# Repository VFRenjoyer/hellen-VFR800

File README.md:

This repo contains files to build a standalone plug and play RusEFI Hellen based ECU for a 99 Honda VFR800. The prototype is unfinished and currently none of these files can be used to make a functioning ECU

This hardware may be compatible with the CBR600F4i, CBR929RR, and 01-03 CBR1100xx  if the ECU connectors were repinned.

In addition to the above it may be able to replace the ignition module/ECU of a 98-08 VT1100C, 01-07 VT750DC, 02-04 VTX1800, RC51, and 2003-09 VTX1300 with some harness repinning

Features in progress as of v0.05A:

Drop in ECU replacement for 99-01 VFR800 with addition of 2 wideband oxygen sensors

4x sequential ignition/injection

CANBUS

2x Wideband oxygen sensor channels

3x lowside driver output on rear connector

Inputs for analog sensor on rear connector

USB support

Bluetooth connectivity

MicroSD card for logging

VSS input to ECU for eventual implementation of traction control

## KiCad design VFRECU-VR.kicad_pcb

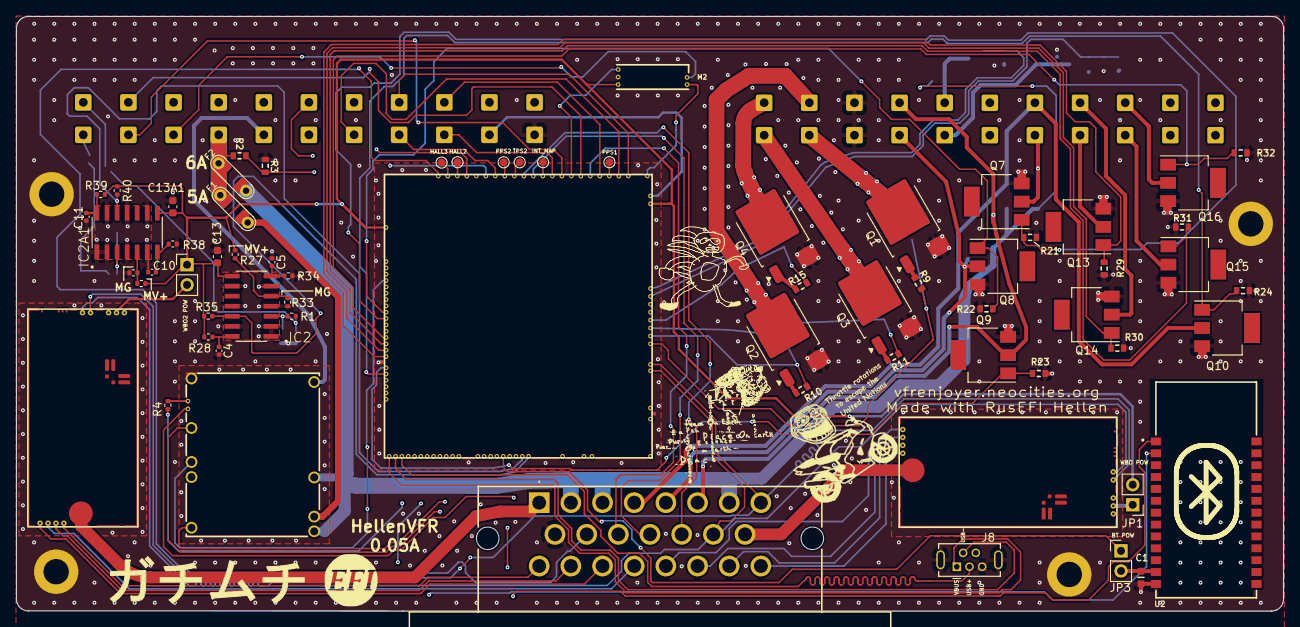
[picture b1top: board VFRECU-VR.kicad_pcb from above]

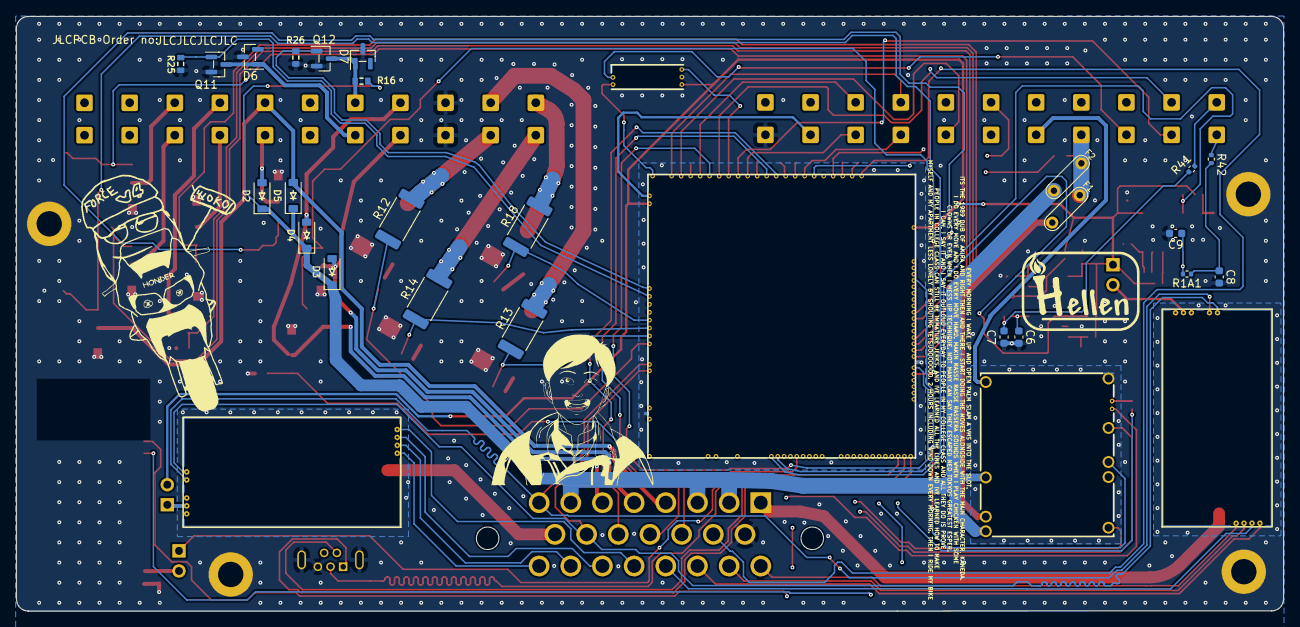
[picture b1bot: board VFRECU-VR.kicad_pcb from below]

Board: 4 copper layers, 160.0 x 75.1 mm, 96 parts (23 on the bottom side), 103 nets.

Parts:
C1: 100n; C0603
C4, C11: 1.2n; C_0402_1005Metric
C5, C10: 0.33u; C_0402_1005Metric
C6, C9: C_0603_1608Metric
C7, C8: 0.33u; C_0603_1608Metric
C13, C13A1: 10u; C_0603_1608Metric
D2, D3, D4, D5: B5819W; SOD-123
D6, D7: PSM712-LF; SOT-23
F1, F2: 12H1500D; PAD-1206-PAD
G3: RUSEFI_LOGO; rusefi_logo
G4: LOGO
H1, H2, H3, H4: MountingHole_Pad; MountingHole_3.2mm_M3_DIN965_Pad
HALL2, HALL3: TestPoint_Pad_D1.0mm
IC2, IC2A1: LM1815MX_NOPB; SOIC127P600X175-14N
INT_MAP: TestPoint_Pad_D1.0mm
J4: 1-776087-1; 17760871
J8: USB_B_Mini; USB-MINI-B-VERTICAL
JP1, JP2, JP3: Jumper_2_Bridged; PinHeader_1x02_P2.54mm_Vertical
M1: Module-power_12and5V-0.2; power_12and5V
M2: Module-knock-0.2; knock
M5, M7: Module-wbo-0.5; wbo
M6: Module:mega-mcu100/0.2; mega-mcu100
PPS1, PPS2: TestPoint_Pad_D1.0mm
Q1, Q2, Q3, Q4: ISL9V3040D3S; TO-252-2
Q7, Q8, Q9, Q10, Q13, Q14, Q15, Q16: ZXMS6005SGTA; SOT-223
Q11, Q12: AO3400A; SOT-23
R1, R1A1: 4.7k; R_0402_1005Metric
R2: 33k; R0603
R3: 6.8k; R0603
R4, R27, R33, R36, R37, R41, R42: 0; R_0402_1005Metric
R9, R10, R11, R15: 22; R0603
R12, R13, R14, R18: 0; R_2512_6332Metric
R16: 470k; R0603
R21, R22, R23, R24, R25, R26, R29, R30, R31, R32: 4.7k; R0603
R28, R39: 100k; R_0402_1005Metric
R34, R38: 1.6M; R_0402_1005Metric
R35, R40: 5.6k; R_0402_1005Metric
TPS2: TestPoint_Pad_D1.0mm
U1: VFRboardempty
U2: JDY-33
text1: trollfaceVFR

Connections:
+3.3VA: JP3.1 (A), M6.N15 (V33_SWITCHABLE)
+5V: M1.E4 (V5), M6.N22 (VCC)
+5VA: C13.2, C13A1.2, IC2.8 (VCC), IC2A1.8 (VCC), JP1.2 (B), JP2.1 (A), M2.E1 (V5A), M6.E1 (V5A_SWITCHABLE), M6.W2 (V5A_SWITCHABLE), R27.1, R28.1, R35.1, R37.1, R39.1, R40.1
+5VP: M1.V4 (5VP), U1.B7
+12V: F1.1, F2.1, R2.2, U1.B8
+12V_RAW: D2.1 (K), D3.1 (K), D4.1 (K), D5.1 (K), F2.2, J4.2, J4.3, J4.7, M1.V1 (V12_PERM), M1.V3 (V12_RAW)
/ADC3: M2.E3 (OUT_KNOCK), M6.S15 (IN_KNOCK_(PA2))
/BARO: M6.S7 (IN_AUX3_(PC5)), U1.B4
/CAM+: R42.1, U1.B11
/CAN+: J4.8, M5.W4 (CANH), M6.W11 (CANH), M7.W4 (CANH)
/CAN-: J4.14, M5.W3 (CANL), M6.W12 (CANL), M7.W3 (CANL)
/CLT: M6.S21 (IN_CLT_(PC2)), U1.B15
/CRANK+: R41.1, U1.B22
/Clutch/kickstandswitch: M6.S16 (IN_CAM_(PA6)), U1.B21
/FILIGHT: D6.1, Q11.2 (D), U1.A7
/FUELPUMP_LS: D2.2 (A), Q7.2 (D), U1.A5
/IAT_SENSOR: M6.S20 (IN_IAT_(PC3)), U1.B5
/IGN1: M6.W10 (IGN1_(PC13)), R9.2, R12.1
/IGN2: M6.W9 (IGN2_(PE5)), R10.2, R13.1
/IGN3: M6.W8 (IGN3_(PE4)), R11.2, R14.1
/IGN4: M6.W7 (IGN4_(PE3)), R15.2, R18.1
/IGNOUT1: Q1.2 (C), R12.2, U1.A10
/IGNOUT2: Q2.2 (C), R13.2, U1.A21
/IGNOUT3: Q3.2 (C), R14.2, U1.A11
/IGNOUT4: Q4.2 (C), R18.2, U1.A22
/INJ1: M6.E17 (OUT_INJ1_(PD3)), Q13.1 (G), R29.2
/INJ2: M6.E16 (OUT_INJ2_(PA9)), Q14.1 (G), R30.2
/INJ3: M6.E15 (OUT_INJ3_(PD11)), Q15.1 (G), R31.2
/INJ4: M6.E14 (OUT_INJ4_(PD10)), Q16.1 (G), R32.2
/INJOUT1: Q13.2 (D), U1.A4
/INJOUT2: Q14.2 (D), U1.A15
/INJOUT3: Q15.2 (D), U1.A3
/INJOUT4: Q16.2 (D), U1.A14
/INTAKEFLAP: D5.2 (A), J4.4, Q10.2 (D), U1.A16
/INTERNAL_MAP: INT_MAP.1, M6.S12 (IN_MAP2_(PC1))
/IN_AUX1: J4.12, M6.S11 (IN_O2S_/_CAN_WAKEUP_(PA0))
/IN_AUX2: J4.13, M6.S10 (IN_O2S2_(PA1))
/IN_BUTTON1: M6.S14 (IN_CRANK_(PB1)), U1.B10
/IN_BUTTON3: J4.10, M6.S1 (IN_D4_(PE15))
/IN_FLEX: J4.11, M6.S17 (IN_VSS_(PE11))
/IN_HALL1: M6.S4 (IN_D1_(PE12)), U1.B17
/IN_HALL2: HALL2.1, M6.S3 (IN_D2_(PE13))
/IN_HALL3: HALL3.1, M6.S2 (IN_D3_(PE14))
/IN_KNOCK_RAW: M2.W1 (IN_KNOCK), U1.B9
/IN_MAP: M6.S13 (IN_MAP1_(PC0)), U1.B3
/IN_PPS1: M6.S19 (IN_PPS_(PA3)), PPS1.1
/IN_PPS2: M6.S8 (IN_AUX2_(PC4/PE9)), PPS2.1
/IN_TPS1: M6.S18 (IN_TPS_(PA4)), U1.B14
/IN_VIGN: F1.2, M1.V2 (IN_VIGN)
/IN_VMAIN: M6.S6 (IN_AUX4_(PA7)), R2.1, R3.2
/LM1815-Cam/Signal+: C8.1, R1A1.1, R42.2
/LM1815-Crank/Signal+: C7.1, R1.1, R41.2
/LS1: M6.E11 (OUT_INJ7_(PD15)), Q7.1 (G), R21.2
/LS2: M6.E10 (OUT_INJ8_(PD12)), Q8.1 (G), R22.2
/LS3: M6.E18 (OUT_PWM1_(PD13)), Q9.1 (G), R23.2
/LS4: M6.E19 (OUT_PWM2_(PC6)), Q10.1 (G), R24.2
/LS_WEAK1: M6.W4 (IGN7_(PB9)), Q11.1 (G), R25.1
/LS_WEAK2: M6.W3 (IGN8_(PE6)), Q12.1 (G), R26.1
/OUT_LS2: D3.2 (A), J4.5, Q8.2 (D), U1.A8
/OUT_LS3: D4.2 (A), J4.6, Q9.2 (D), U1.A19
/OUT_LS_WEAK2: D7.1, Q12.2 (D), R16.1, U1.A18
/PG_5VP: M6.N12 (SPI3_MOSI_(PC12)), R4.2
/PWR_EN: M1.E5 (EN_5VP), M6.N20 (OUT_PWR_EN_(PE10))
/USB+: J8.3 (D+), M6.N3 (USBP_(PA12))
/USB-: J8.2 (D-), M6.N2 (USBM_(PA11))
/VBAT: M1.E1 (VBAT), M6.N17 (VBAT)
/VBUS: J8.1 (VBUS), M6.N1 (VBUS)
/VIGN: M1.E3 (VIGN), M6.E5 (IN_VIGN_(PA5))
/VR1: IC2A1.12 (REFERENCE_PULSE_OUT), M6.N18 (UART8_RX_(PE0)), R40.2
/VR2: IC2.12 (REFERENCE_PULSE_OUT), M6.N19 (UART8_TX_(PE1)), R35.2
/VREF1: M2.W2 (VREF), M6.S22 (VREF1)
/WBO2_Heater: J4.1, M7.E5 (LSU_H+)
/WBO2_Ip: J4.17, M7.E3 (LSU_Ip)
/WBO2_Rtrim: J4.19, M7.E4 (LSU_Rtrim)
/WBO2_Un: J4.18, M7.E1 (LSU_Un)
/WBO2_Vm: J4.16, M7.E2 (LSU_Vm)
/WBO_Heater: J4.15, M5.E5 (LSU_H+)
/WBO_Ip: J4.22, M5.E3 (LSU_Ip)
/WBO_Rtrim: J4.21, M5.E4 (LSU_Rtrim)
/WBO_Un: J4.20, M5.E1 (LSU_Un)
/WBO_Vm: J4.23, M5.E2 (LSU_Vm)
GND: C1.1, C4.2, C5.1, C6.2, C7.2, C8.2, C9.2, C10.1, C11.2, C13.1, C13A1.1, D6.2, D7.2, H1.1, H2.1, H3.1, H4.1, IC2.1 (NC_1), IC2.2 (GND), IC2.4 (NC_2), IC2.6 (NC_3), IC2.9 (TIMING_PULSE_INPUT), IC2.11 (INPUT_SELECT), IC2.13 (NC_4), IC2A1.1 (NC_1), IC2A1.2 (GND), IC2A1.4 (NC_2), IC2A1.6 (NC_3), IC2A1.9 (TIMING_PULSE_INPUT), IC2A1.11 (INPUT_SELECT), IC2A1.13 (NC_4), J4.9, J8.5 (GND), J8.6 (Shield), M1.S1 (GND), M2.E2 (GND), M5.E6 (LSU_H-), M5.G (GND), M6.G (GND), M7.E6 (LSU_H-), M7.G (GND), Q1.3 (E), Q2.3 (E), Q3.3 (E), Q4.3 (E), Q7.3 (S), Q8.3 (S), Q9.3 (S), Q10.3 (S), Q11.3 (S), Q12.3 (S), Q13.3 (S), Q14.3 (S), Q15.3 (S), Q16.3 (S), R3.1, R21.1, R22.1, R23.1, R24.1, R25.2, R26.2, R29.1, R30.1, R31.1, R32.1, R33.1, R34.2, R36.1, R38.2, U1.A9, U1.A20, U1.B1, U1.B12, U2.13 (GND)
GNDA: M6.W1 (GNDA), U1.B2
unnamed: IC2.5 (MODE), R27.2, R33.2
unnamed: C5.2, IC2.7 (PEAK_DETECTOR_CAPACITOR), R34.1
unnamed: C4.1, IC2.14 (RC_TIMING), R28.2
unnamed: C6.1, IC2.3 (VIN), R1.2
unnamed: IC2A1.5 (MODE), R36.2, R37.2
unnamed: C10.2, IC2A1.7 (PEAK_DETECTOR_CAPACITOR), R38.1
unnamed: C11.1, IC2A1.14 (RC_TIMING), R39.2
unnamed: C9.1, IC2A1.3 (VIN), R1A1.2
unnamed: JP1.1 (A), M5.W1 (V5_IN)
unnamed: JP2.2 (B), M7.W1 (V5_IN)
unnamed: C1.2, JP3.2 (B), U2.12 (3V3)
unnamed: M1.E6 (PG_5VP), R4.1
unnamed: M5.J1 (SEL1), M5.J_GND1 (PULL_DOWN1)
unnamed: M6.N14 (UART2_RX_(PD6)), U2.1 (TXD)
unnamed: M6.N13 (UART2_TX_(PD5)), U2.2 (RXD)
unnamed: M7.J1 (SEL1), M7.J_GND1 (PULL_DOWN1)
unnamed: Q1.1 (G), R9.1
unnamed: Q2.1 (G), R10.1
unnamed: Q3.1 (G), R11.1
unnamed: Q4.1 (G), R15.1

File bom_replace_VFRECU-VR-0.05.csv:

"Id";"Designator";"Footprint";"Quantity";"Designation";"Supplier and ref";
1;"J4";"17760871";1;"1-776087-1";;;
2;"IC2A1,IC2";"SOIC127P600X175-14N";2;"LM1815MX_NOPB";;;
3;"Q7,Q9,Q14,Q13,Q8,Q15,Q10,Q16";"SOT-223";8;"ZXMS6005SGTA";;;
4;"R32,R31,R29,R30,R22,R21,R24,R23,R26,R25";"R0603";10;"4.7k";;;
5;"R34,R38";"R_0402_1005Metric";2;"1.6M";;;
6;"C4,C11";"C_0402_1005Metric";2;"1.2n";;;
7;"Q1,Q4,Q3,Q2";"TO-252-2";4;"ISL9V3040D3S";;;
8;"R39,R28";"R_0402_1005Metric";2;"100k";;;
9;"R40,R35";"R_0402_1005Metric";2;"5.6k";;;
10;"H2,H1,H2,H3";"MountingHole_3.2mm_M3_DIN965_Pad";4;"MountingHole_Pad";;;
11;"R27,R37,R33,R36,R42,R41";"R_0402_1005Metric";6;"0";;;
12;"C10,C5";"C_0402_1005Metric";2;"0.33u";;;
13;"JP3,JP2,JP1";"PinHeader_1x02_P2.54mm_Vertical";3;"Jumper_2_Bridged";;;
14;"C12A1,C3";"C_0402_1005Metric";2;"100n";;;
15;"R2";"R0603";1;"33k";;;
16;"M7,M5";"wbo";2;"Module-wbo-0.5";;;
17;"M1";"power_12and5V";1;"Module-power_12and5V-0.2";;;
18;"C1";"C0603";1;"100n";;;
19;"R10,R11,R9,R15";"R0603";4;"22";;;
20;"U1";"VFRboardempty";1;"~";;;
21;"text1";"trollfaceVFR";1;"~";;;
22;"J8";"USB-MINI-B-VERTICAL";1;"USB_B_Mini";;;
23;"C13A1,C13";"C_0603_1608Metric";2;"1u";;;
24;"F2,F1";"PAD-1206-PAD";2;"12H1500D";;;
25;"M6";"mega-mcu100";1;"Module:mega-mcu100/0.2";;;
26;"U2";"JDY-33";1;"JDY-33";;;
27;"G3";"rusefi_logo";1;"RUSEFI_LOGO";;;
28;"R3";"R0603";1;"6.8k";;;
29;"R1,R1A1";"R_0402_1005Metric";2;"4.7k";;;
30;"G4";"LOGO";1;"LOGO";;;
31;"C7,C8";"C_0603_1608Metric";2;"0.33u";;;
32;"C9,C6";"C_0603_1608Metric";2;"~";;;
33;"R16";"R0603";1;"470k";;;
34;"D2,D5,D3,D4";"SOD-123";4;"B5819W";;;
35;"R12,R18,R13,R14";"R_2512_6332Metric";4;"0";;;
36;"D7,D6";"SOT-23";2;"PSM712-LF";;;
37;"Q12,Q11";"SOT-23";2;"AO3400A";;;

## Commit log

2024-04-19 [skip actions] Auto-generated board v2.1
2024-04-27 Mounting holes and resistor
    Added a mounting hole for the case, moved existing hole closer to corner, populated ADC3 resistor
2024-04-28 Holes and VR
    Rearranged bolt hole and VR conditioner to move hole closer to board edge
2024-04-28 Added ref to hole
2024-04-29 GHA says update hellen-one
2024-05-18 GHA says update kicad6-libraries
2024-05-27 Added spreadsheet with 0.04 rev A hardware fixes
2024-05-27 Added VR- offset resistors and pads for unused analog/hall inputs
2024-05-27 fixed R17 silkscreen overlapping pad
2025-01-03 minor changes to cam signal routing
2025-01-04 H4 properties fix so scripts run
2025-01-05 Changed to LM1815 for VR sensing, incremented revision to 0.05
2025-01-05 Added DNP parts to kicad bom
2025-01-05 Trying to make BOM work
2025-01-05 Fixed mismatch between part designators?
2025-01-06 Missed two designators
2025-01-06 Don't need proofreading I'm a FREAK
2025-01-06 Removed vestigial pull up resistors on cam/crank - pins
2025-01-06 Edited designator instead of label
2025-01-06 More Designations
2025-01-06 Removed incorrect part number
2025-01-06 Fixed BOM filename
2025-01-06 Cleared BOM
2025-01-06 Deleted old files
2025-01-29 Lots of routing changes
    Read some papers by TI during a jenkem binge and hopefully improved the PCB layout
2025-01-29 Changed Routing
2025-01-30 Added art, routing changes
2025-01-30 removed backups folder
2025-01-30 More art
2025-01-30 simplified graphics
2025-02-03 More routing changes
2025-02-03 Fixed references
2025-02-05 Moved Ground Planes to Internal Layers
2025-02-05 Beautified Routing
2025-02-05 Further improved routing
2025-02-05 Routing and Silkscreen Improvements
2025-02-05 More routing
2025-02-05 Even more routing
2025-02-05 Changed ground vias on ignition drivers
2025-02-05 fixed routing on in_aux_2
2025-02-06 Fixed pads
2025-02-06 Routing
2025-02-06 Routing changes
2025-02-06 made ground planes better
2025-02-06 Removed via floating in space
2025-02-10 Changed component sizes, added stitching vias
2025-02-10 Changed ignition driver pad
2025-02-10 via fence around WBO heater
2025-02-10 Removed garbage
2025-02-13 Added knock detection hardware
2025-02-13 Fixed some DRC callouts
2025-02-18 Cleared ground plane under antenna
2025-02-18 Ground plane and via changes
2025-02-24 Via changes and routing
2025-03-01 vias and silkscreen changes
2026-05-14 Replace Vias
